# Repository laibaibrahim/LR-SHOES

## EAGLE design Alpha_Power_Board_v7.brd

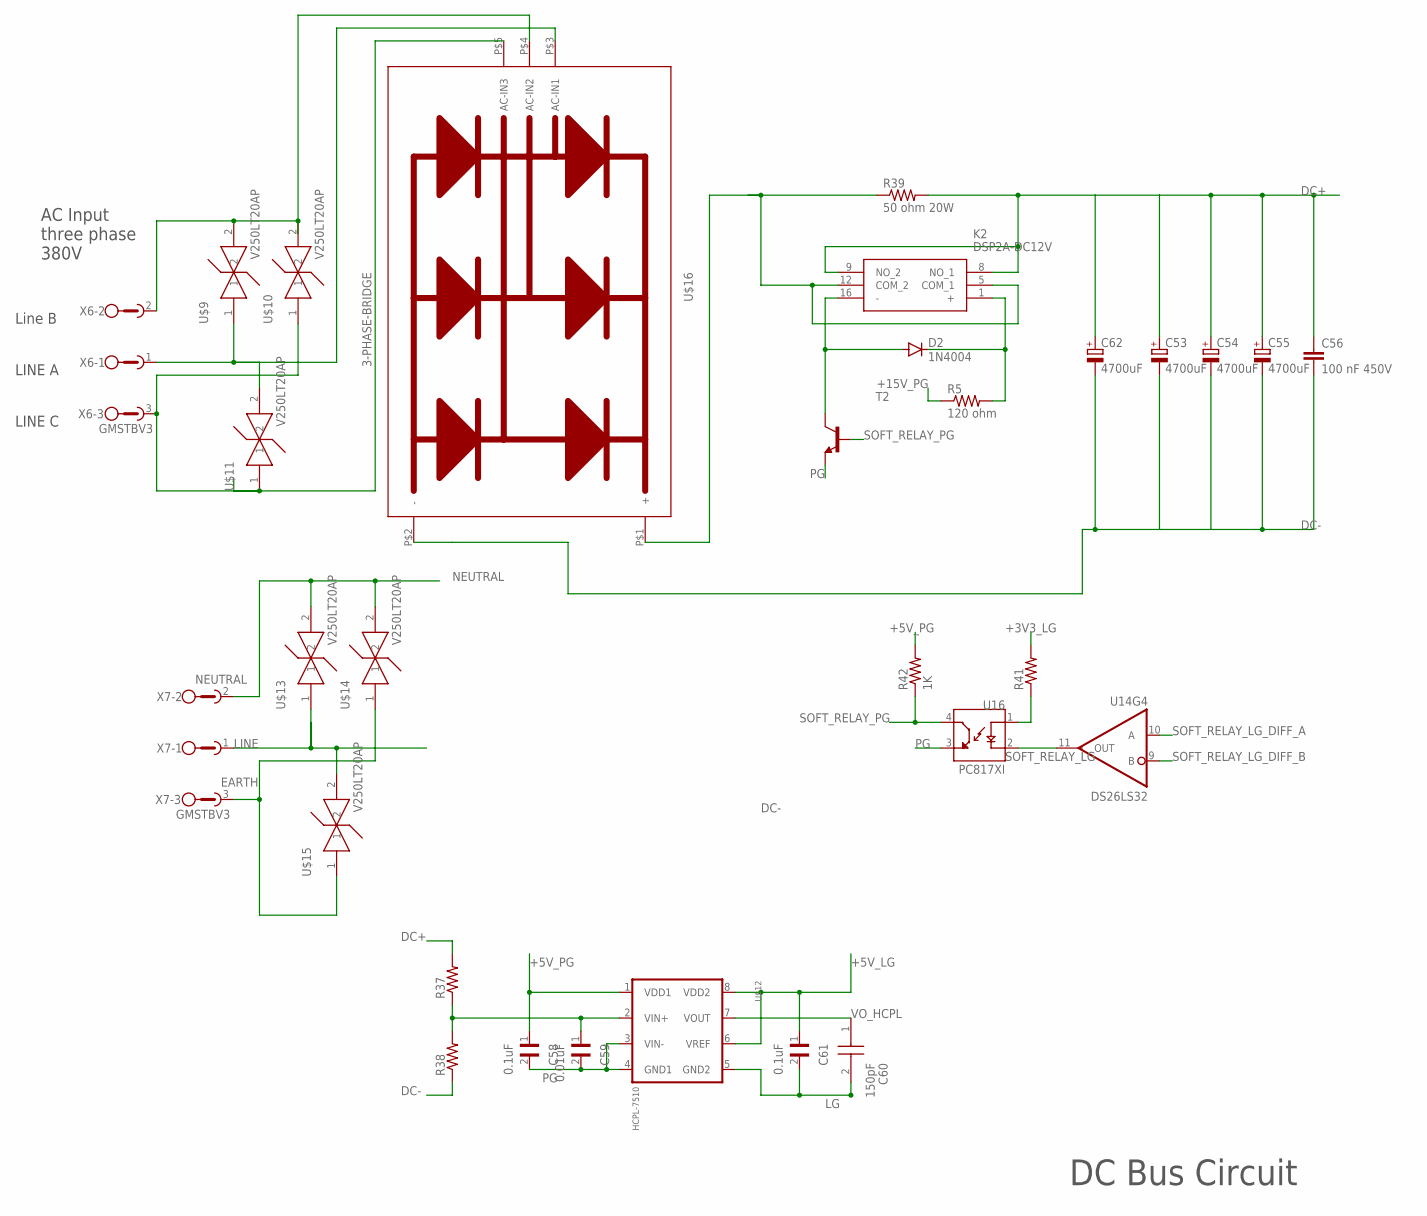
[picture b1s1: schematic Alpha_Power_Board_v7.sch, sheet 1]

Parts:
C53, C54, C55, C62: 4700uF; EB35D
C56: 100 nF 450V; C102-064X133
C58, C61: 0.1uF; CAPC3316X140N
C59: 0.01uF; CAPC3316X140N
C60: 150pF; CAP150PF
D2: 1N4004; DO41-10
K2: DSP2A-DC12V; DSP2ADC12V
R5: 120 ohm; 0207/15
R37, R38: R-US_0309/12; 0309/12
R39: 50 ohm 20W; B20J50RE
R41: R-US_R1206; R1206
R42: 1K; R1206
T2: MMBT2222ALT1-NPN-SOT23-BEC; SOT23-BEC
U14: DS26LS32; SOIC_16
U16: PC817XI; SOIC254P975X460-4N
U$9, U$10, U$11, U$13, U$14, U$15: V250LT20AP
U$12: HCPL-7510
U$16: 3-PHASE-BRIDGE
X6, X7: GMSTBV3

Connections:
+3V3_LG: R41.2; also elsewhere on the board
+5V_LG: C61.1, U$12.6 (VREF), U$12.8 (VDD2); also elsewhere on the board
+5V_PG: C58.1, R42.2, U$12.1 (VDD1); also elsewhere on the board
+15V_PG: R5.1; also elsewhere on the board
DC+: C53.+, C54.+, C55.+, C56.1, C62.+, K2.8 (NO_1), K2.9 (NO_2), R37.2, R39.2; also elsewhere on the board
DC-: C53.-, C54.-, C55.-, C56.2, C62.-, R38.1, U$16.P$2 (-); also elsewhere on the board
EARTH: U$14.1, U$15.1, X7.3
L1: U$9.1, U$11.2, U$16.P$3 (AC-IN1), X6.1
L2: U$9.2, U$10.2, U$16.P$4 (AC-IN2), X6.2
L3: U$10.1, U$11.1, U$16.P$5 (AC-IN3), X6.3
LG: C60.2, C61.2, U$12.5 (GND2); also elsewhere on the board
LINE: U$13.1, U$15.2, X7.1; also elsewhere on the board
unnamed: C59.1, R37.1, R38.2, U$12.2 (VIN+)
unnamed: D2.C, K2.1 (+), R5.2
unnamed: D2.A, K2.16 (-), T2.C
unnamed: R41.1, U16.1 (A)
unnamed: K2.5 (COM_1), K2.12 (COM_2), R39.1, U$16.P$1 (+)
NEUTRAL: U$13.2, U$14.2, X7.2; also elsewhere on the board
PG: C58.2, C59.2, T2.E, U16.3 (ET), U$12.3 (VIN-), U$12.4 (GND1); also elsewhere on the board
SOFT_RELAY_LG: U14.11 (OUT), U16.2 (C)
SOFT_RELAY_LG_DIFF_A: U14.10 (A); also elsewhere on the board
SOFT_RELAY_LG_DIFF_B: U14.9 (B); also elsewhere on the board
SOFT_RELAY_PG: R42.1, T2.B, U16.4 (CT)
VO_HCPL: C60.1, U$12.7 (VOUT); also elsewhere on the board

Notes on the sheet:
DC Bus Circuit
AC Input three phase 380V
Line B
LINE C
LINE A

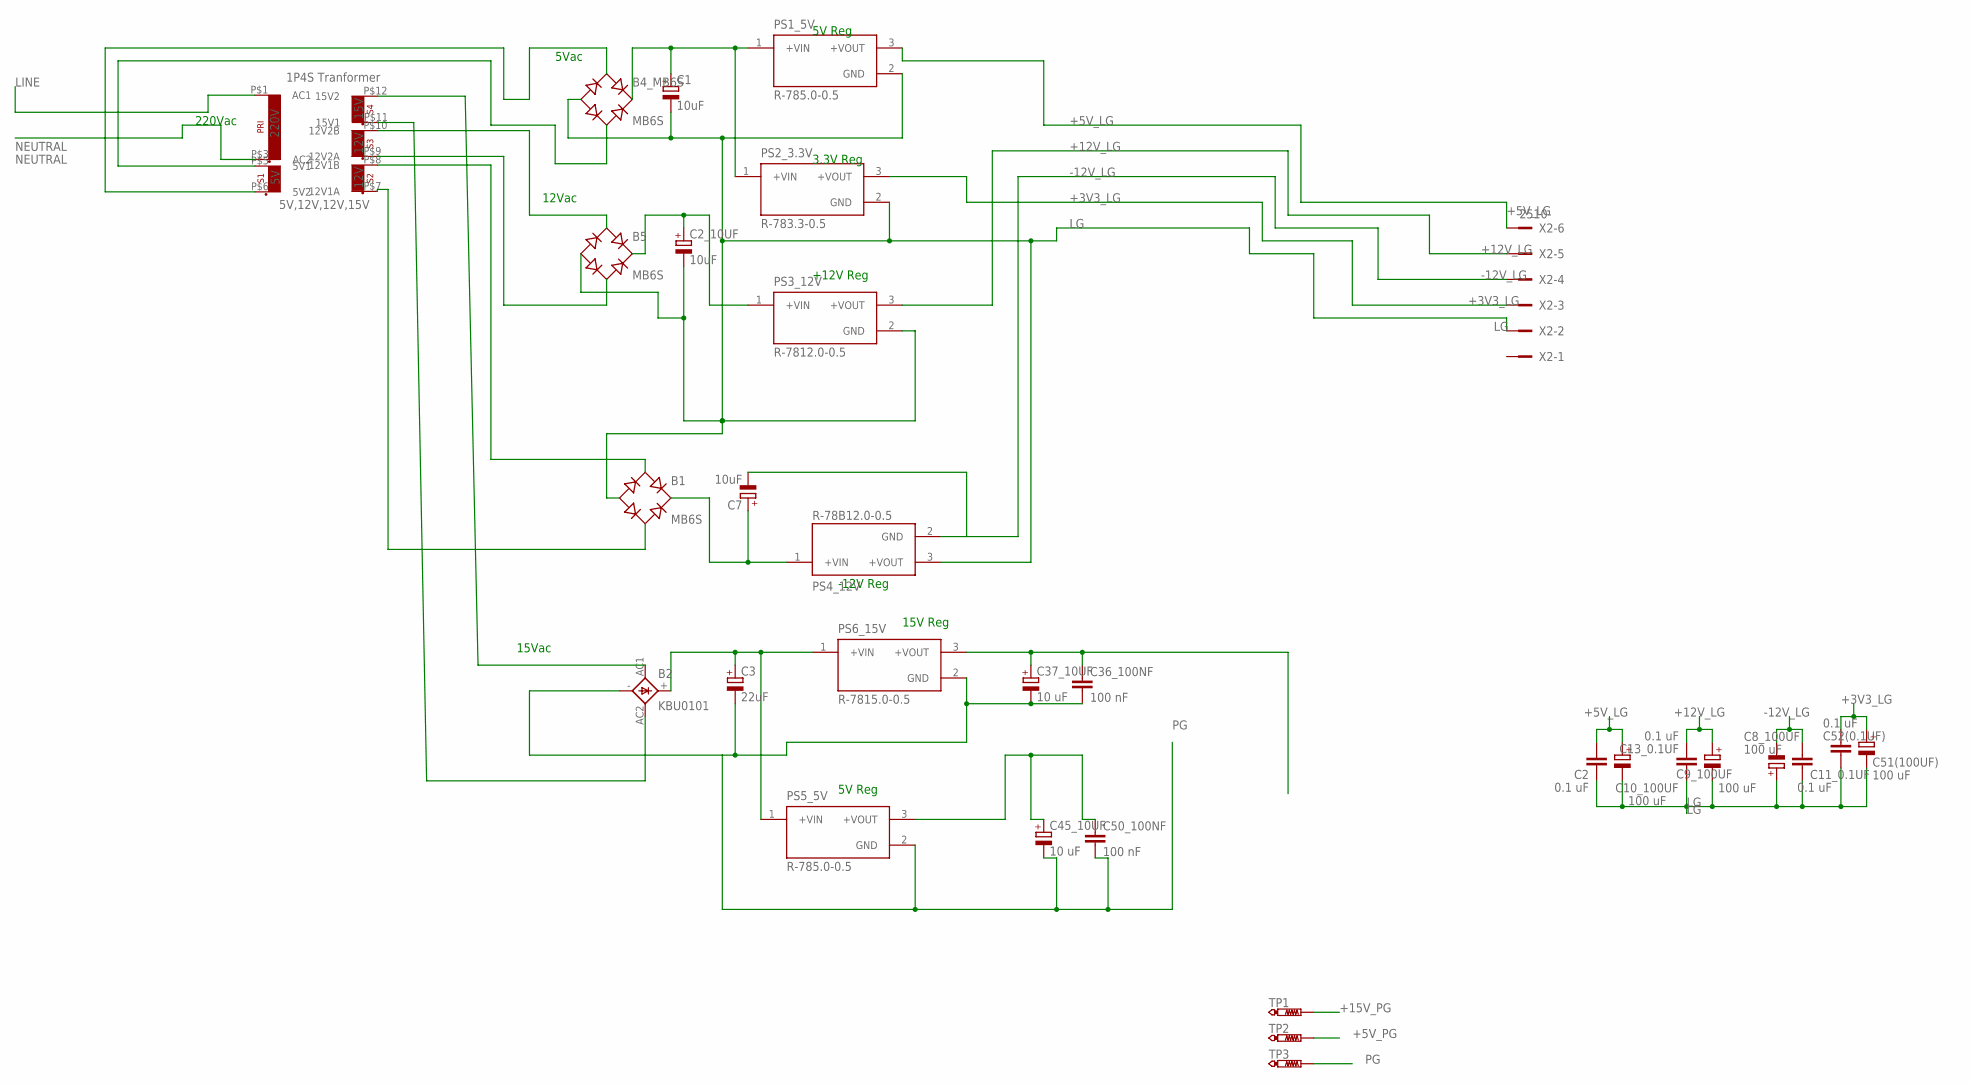
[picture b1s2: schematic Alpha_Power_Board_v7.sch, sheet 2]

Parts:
B1, B4_MB6S, B5: MB6S; SOIC-4
B2: KBU0101; KBU
C1, C2_10UF, C7: 10uF; E2,5-6E
C2, C11_0.1UF, C13_0.1UF, C52(0.1UF): 0.1 uF; C1206
C3: 22uF; E2,5-6E
C8_100UF, C9_100UF, C10_100UF, C51(100UF): 100 uF; 153CLV-0605
C36_100NF, C50_100NF: 100 nF; C025-025X050
C37_10UF, C45_10UF: 10 uF; TT2D5
PS1_5V, PS5_5V: R-785.0-0.5; CONV_R-78E5.0-0.5
PS2_3.3V: R-783.3-0.5; CONV_R-78E5.0-0.5
PS3_12V: R-7812.0-0.5; CONV_R-78E5.0-0.5
PS4_12V: R-78B12.0-0.5; CONV_R-78E5.0-0.5
PS6_15V: R-7815.0-0.5; CONV_R-78E5.0-0.5
TP1, TP2, TP3: PTR1PAD1-13; P1-13
U$1: TRANSFORMERTHROUGH-HOLE; T1P2S
X2: 2510-; PAK100/2500-10

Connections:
+3V3_LG: C51(100UF).+, C52(0.1UF).1, PS2_3.3V.3 (+VOUT), X2.3; also elsewhere on the board
+5V_LG: C2.1, C10_100UF.+, PS1_5V.3 (+VOUT), X2.6; also elsewhere on the board
+5V_PG: C45_10UF.+, C50_100NF.1, PS5_5V.3 (+VOUT), TP2.TP; also elsewhere on the board
+12V_LG: C9_100UF.+, C13_0.1UF.1, PS3_12V.3 (+VOUT), X2.5; also elsewhere on the board
+15V_PG: C36_100NF.1, C37_10UF.+, PS6_15V.3 (+VOUT), TP1.TP; also elsewhere on the board
-12V_LG: C7.-, C8_100UF.-, C11_0.1UF.1, PS4_12V.2 (GND), X2.4; also elsewhere on the board
LG: B1.-, B4_MB6S.-, B5.-, C1.-, C2.2, C2_10UF.-, C8_100UF.+, C9_100UF.-, C10_100UF.-, C11_0.1UF.2, C13_0.1UF.2, C51(100UF).-, C52(0.1UF).2, PS1_5V.2 (GND), PS2_3.3V.2 (GND), PS3_12V.2 (GND), PS4_12V.3 (+VOUT), X2.2; also elsewhere on the board
LINE: U$1.P$1 (AC1); also elsewhere on the board
unnamed: B4_MB6S.~2 (AC2), U$1.P$5 (5V1)
unnamed: B5.~1 (AC1), U$1.P$10 (12V2B)
unnamed: B5.~2 (AC2), U$1.P$9 (12V2A)
unnamed: B5.+, C2_10UF.+, PS3_12V.1 (+VIN)
unnamed: B2.AC1, U$1.P$12 (15V2)
unnamed: B2.AC2, U$1.P$11 (15V1)
unnamed: B4_MB6S.~1 (AC1), U$1.P$6 (5V2)
unnamed: B1.~1 (AC1), U$1.P$8 (12V1B)
unnamed: B1.~2 (AC2), U$1.P$7 (12V1A)
unnamed: B1.+, C7.+, PS4_12V.1 (+VIN)
unnamed: B2.+, C3.+, PS5_5V.1 (+VIN), PS6_15V.1 (+VIN)
unnamed: B4_MB6S.+, C1.+, PS1_5V.1 (+VIN), PS2_3.3V.1 (+VIN)
NEUTRAL: U$1.P$3 (AC2); also elsewhere on the board
PG: B2.-, C3.-, C36_100NF.2, C37_10UF.-, C45_10UF.-, C50_100NF.2, PS5_5V.2 (GND), PS6_15V.2 (GND), TP3.TP; also elsewhere on the board

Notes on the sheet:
5Vac
5V Reg
3.3V Reg
12Vac
+12V Reg
15Vac
220Vac
15V Reg
-12V Reg

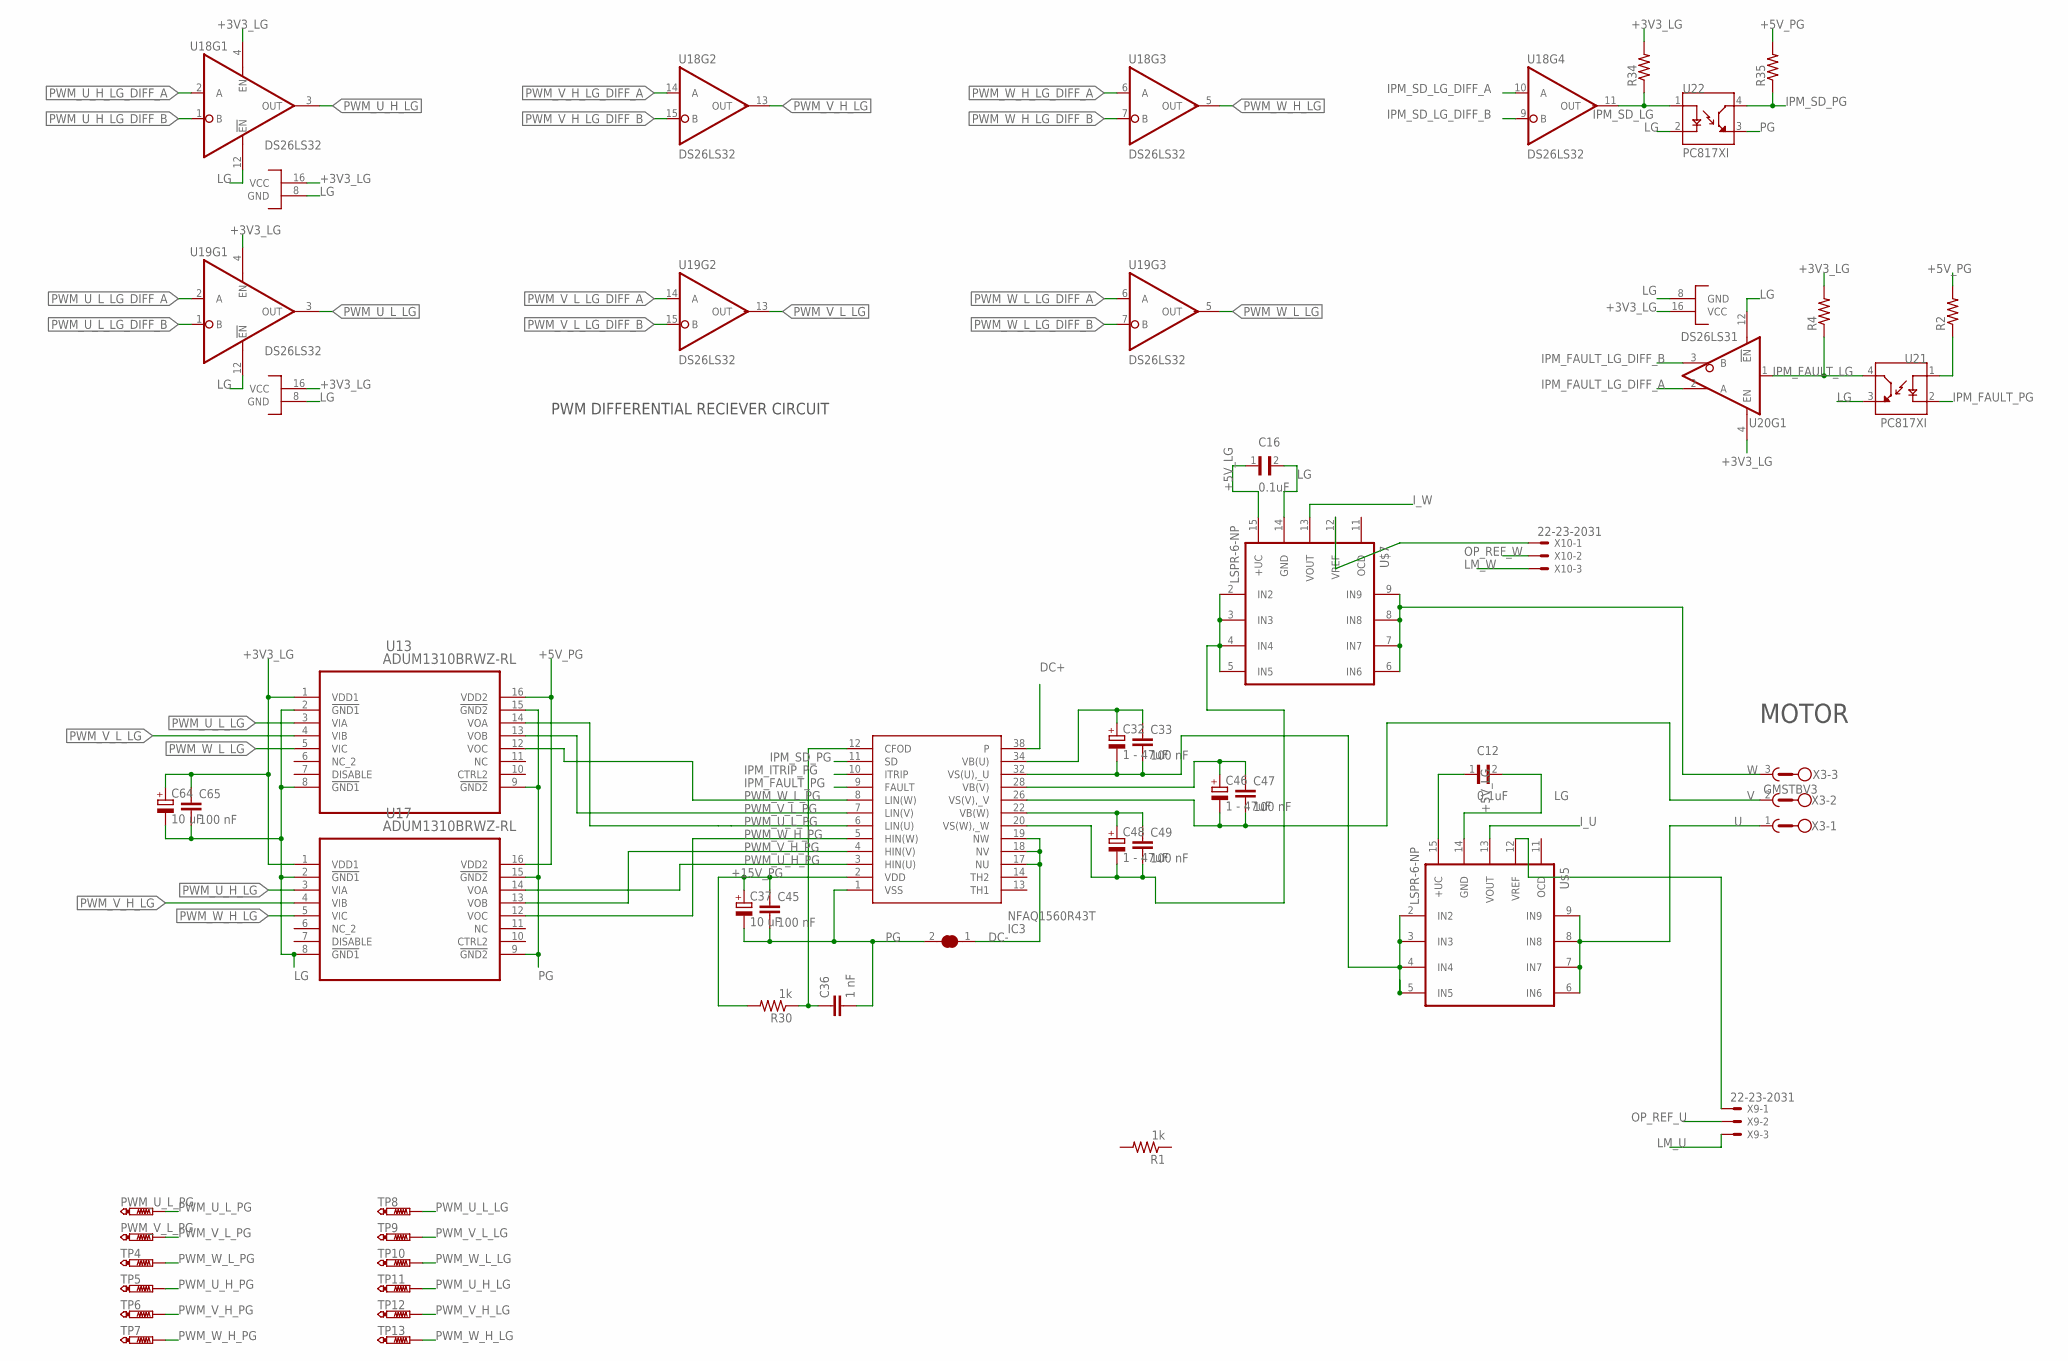
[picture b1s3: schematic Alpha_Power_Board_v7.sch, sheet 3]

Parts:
C12, C16: 0.1uF; CAPC3316X140N
C32, C46, C48: 1 - 47uF; E3,5-8
C33, C47, C49: 100 nF; C025-030X050
C36: 1 nF; C025-025X050
C37: 10 uF; TT2D5
C45: 100 nF; C025-025X050
C64: 10 uF; SMC_P
C65: 100 nF; C1206
IC3: NFAQ1560R43T
PWM_U_L_PG: PTR1PAD1-13; P1-13
PWM_V_L_PG: PTR1PAD1-13; P1-13
R1, R30: 1k; 0204V
R2, R4: R-US_R1206; R1206
R34: R-US_R0805W; R0805W
R35: R-US_R0805; R0805
TP4, TP5, TP6, TP7, TP8, TP9, TP10, TP11, TP12, TP13: PTR1PAD1-13; P1-13
U13, U17: ADUM1310BRWZ-RL; RW_16_ADI
U18, U19: DS26LS32; SOIC_16
U20: DS26LS31; SOIC_16
U21, U22: PC817XI; SOIC254P975X460-4N
U$2: GND_CONNECT
U$5, U$7: LSPR-6-NP; LPSR-15-NP
X3: GMSTBV3
X9, X10: 22-23-2031

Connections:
+3V3_LG: C64.+, C65.1, R4.2, R34.2, U13.1 (VDD1), U17.1 (VDD1), U18.4 (EN), U18.16 (VCC), U19.4 (EN), U19.16 (VCC), U20.4 (EN), U20.16 (VCC); also elsewhere on the board
+5V_LG: C12.1, C16.1, U$5.15 (+UC), U$7.15 (+UC); also elsewhere on the board
+5V_PG: R2.2, R35.2, U13.16 (VDD2), U17.16 (VDD2); also elsewhere on the board
+15V_PG: C37.+, C45.1, IC3.2 (VDD), R30.2; also elsewhere on the board
DC+: IC3.38; also elsewhere on the board
DC-: IC3.17 (NU), IC3.18 (NV), IC3.19 (NW), U$2.1; also elsewhere on the board
IPM_FAULT_LG: R4.1, U20.1 (IN), U21.4 (CT)
IPM_FAULT_LG_DIFF_A: U20.2 (A); also elsewhere on the board
IPM_FAULT_LG_DIFF_B: U20.3 (B); also elsewhere on the board
IPM_FAULT_PG: IC3.9 (FAULT), U21.2 (C)
IPM_ITRIP_PG: IC3.10 (ITRIP)
IPM_SD_LG: R34.1, U18.11 (OUT), U22.1 (A)
IPM_SD_LG_DIFF_A: U18.10 (A); also elsewhere on the board
IPM_SD_LG_DIFF_B: U18.9 (B); also elsewhere on the board
IPM_SD_PG: IC3.11 (SD), R35.1, U22.4 (CT)
I_U: U$5.13 (VOUT); also elsewhere on the board
I_W: U$7.13 (VOUT); also elsewhere on the board
LG: C12.2, C16.2, C64.-, C65.2, U13.2 (!GND1), U13.8 (!GND1), U17.2 (!GND1), U17.8 (!GND1), U18.8 (GND), U18.12 (!EN), U19.8 (GND), U19.12 (!EN), U20.8 (GND), U20.12 (!EN), U21.3 (ET), U22.2 (C), U$5.14 (GND), U$7.14 (GND); also elsewhere on the board
LM_U: X9.3; also elsewhere on the board
LM_W: X10.3; also elsewhere on the board
unnamed: R2.1, U21.1 (A)
unnamed: U$5.12 (VREF), X9.1
unnamed: C32.-, C33.2, IC3.32 (VS(U),_U), U$5.2 (IN2), U$5.3 (IN3), U$5.4 (IN4), U$5.5 (IN5)
unnamed: U$7.12 (VREF), X10.1
unnamed: C32.+, C33.1, IC3.34 (VB(U))
unnamed: C48.+, C49.1, IC3.22 (VB(W))
unnamed: C48.-, C49.2, IC3.20 (VS(W),_W), U$7.2 (IN2), U$7.3 (IN3), U$7.4 (IN4), U$7.5 (IN5)
unnamed: C46.+, C47.1, IC3.28 (VB(V))
unnamed: C36.1, IC3.12 (CFOD), R30.1
OP_REF_U: X9.2; also elsewhere on the board
OP_REF_W: X10.2; also elsewhere on the board
PG: C36.2, C37.-, C45.2, IC3.1 (VSS), U13.9 (!GND2), U13.15 (!GND2), U17.9 (!GND2), U17.15 (!GND2), U22.3 (ET), U$2.2; also elsewhere on the board
PWM_U_H_LG: TP11.TP, U17.3 (VIA), U18.3 (OUT)
PWM_U_H_LG_DIFF_A: U18.2 (A); also elsewhere on the board
PWM_U_H_LG_DIFF_B: U18.1 (B); also elsewhere on the board
PWM_U_H_PG: IC3.3 (HIN(U)), TP5.TP, U17.14 (VOA)
PWM_U_L_LG: TP8.TP, U13.3 (VIA), U19.3 (OUT)
PWM_U_L_LG_DIFF_A: U19.2 (A); also elsewhere on the board
PWM_U_L_LG_DIFF_B: U19.1 (B); also elsewhere on the board
PWM_U_L_PG: IC3.6 (LIN(U)), PWM_U_L_PG.TP, U13.14 (VOA)
PWM_V_H_LG: TP12.TP, U17.4 (VIB), U18.13 (OUT)
PWM_V_H_LG_DIFF_A: U18.14 (A); also elsewhere on the board
PWM_V_H_LG_DIFF_B: U18.15 (B); also elsewhere on the board
PWM_V_H_PG: IC3.4 (HIN(V)), TP6.TP, U17.13 (VOB)
PWM_V_L_LG: TP9.TP, U13.4 (VIB), U19.13 (OUT)
PWM_V_L_LG_DIFF_A: U19.14 (A); also elsewhere on the board
PWM_V_L_LG_DIFF_B: U19.15 (B); also elsewhere on the board
PWM_V_L_PG: IC3.7 (LIN(V)), PWM_V_L_PG.TP, U13.13 (VOB)
PWM_W_H_LG: TP13.TP, U17.5 (VIC), U18.5 (OUT)
PWM_W_H_LG_DIFF_A: U18.6 (A); also elsewhere on the board
PWM_W_H_LG_DIFF_B: U18.7 (B); also elsewhere on the board
PWM_W_H_PG: IC3.5 (HIN(W)), TP7.TP, U17.12 (VOC)
PWM_W_L_LG: TP10.TP, U13.5 (VIC), U19.5 (OUT)
PWM_W_L_LG_DIFF_A: U19.6 (A); also elsewhere on the board
PWM_W_L_LG_DIFF_B: U19.7 (B); also elsewhere on the board
PWM_W_L_PG: IC3.8 (LIN(W)), TP4.TP, U13.12 (VOC)
U: U$5.6 (IN6), U$5.7 (IN7), U$5.8 (IN8), U$5.9 (IN9), X3.1
V: C46.-, C47.2, IC3.26 (VS(V),_V), X3.2
W: U$7.6 (IN6), U$7.7 (IN7), U$7.8 (IN8), U$7.9 (IN9), X3.3

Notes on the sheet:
MOTOR
PWM DIFFERENTIAL RECIEVER CIRCUIT

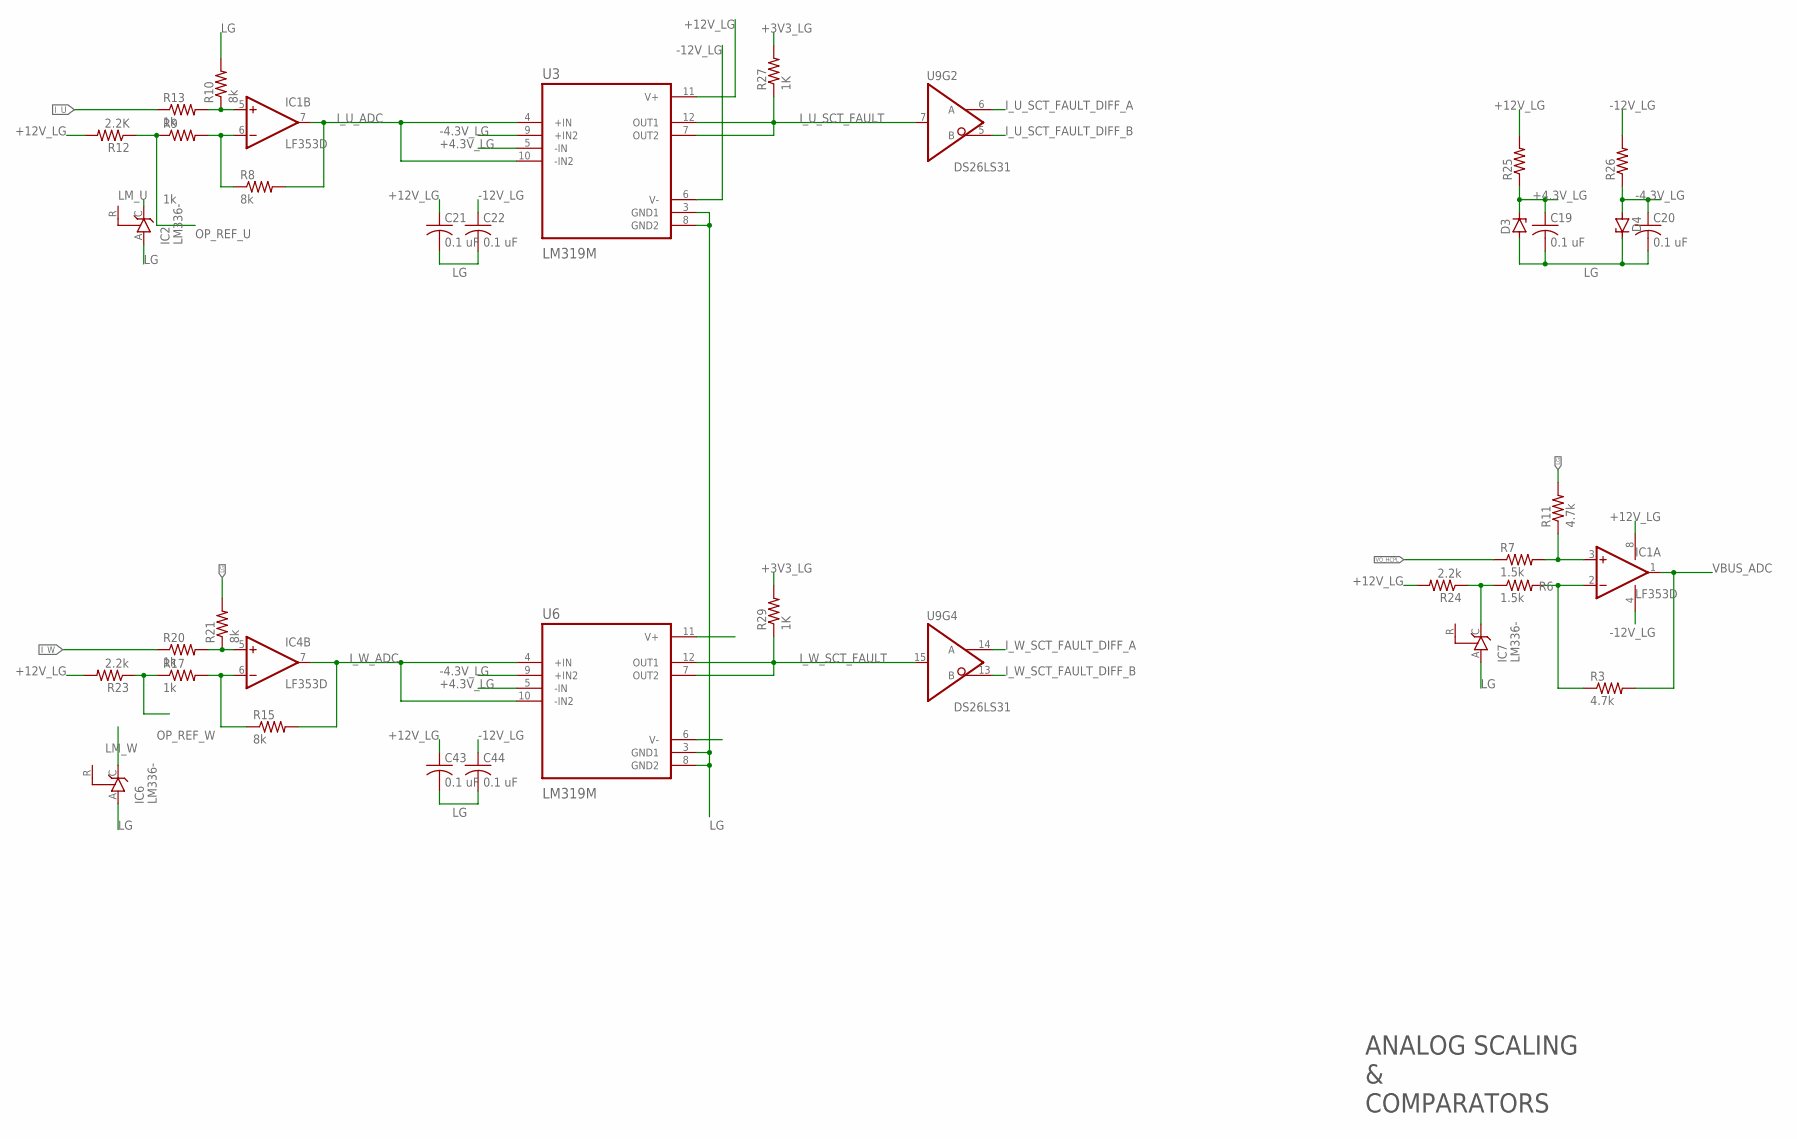
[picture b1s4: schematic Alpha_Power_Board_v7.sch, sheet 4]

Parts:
C19, C20, C21, C22, C43, C44: 0.1 uF; C1206
D3, D4: ZENER-DIODETO236; TO236
IC1, IC4: LF353D; SO08
IC2, IC6, IC7: LM336-; TO92A_VREF
R3, R11: 4.7k; M1206
R6: 1.5k; M1206
R7: 1.5k; R1206
R8, R10, R15, R21: 8k; M1206
R9, R13, R17, R20: 1k; M1206
R12: 2.2K; M1206
R23, R24: 2.2k; M1206
R25, R26: R-US_M1206; M1206
R27, R29: 1K; R1206
U3, U6: LM319M; SOIC127P600X175-14N
U9: DS26LS31; SOIC_16

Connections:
+3V3_LG: R27.2, R29.2; also elsewhere on the board
+4.3V_LG: C19.1, D3.C, R25.1, U3.5 (-IN), U6.5 (-IN)
+12V_LG: C21.1, C43.1, IC1.8 (V+), R12.2, R23.2, R24.2, R25.2, U3.11 (V+); also elsewhere on the board
-4.3V_LG: C20.1, D4.A, R26.1, U3.9 (+IN2), U6.9 (+IN2)
-12V_LG: C22.1, C44.1, IC1.4 (V-), R26.2, U3.6 (V-); also elsewhere on the board
I_U: R13.1; also elsewhere on the board
I_U_ADC: IC1.7 (OUT), R8.2, U3.4 (+IN), U3.10 (-IN2); also elsewhere on the board
I_U_SCT_FAULT: R27.1, U3.7 (OUT2), U3.12 (OUT1), U9.7 (IN)
I_U_SCT_FAULT_DIFF_A: U9.6 (A); also elsewhere on the board
I_U_SCT_FAULT_DIFF_B: U9.5 (B); also elsewhere on the board
I_W: R20.1; also elsewhere on the board
I_W_ADC: IC4.7 (OUT), R15.2, U6.4 (+IN), U6.10 (-IN2); also elsewhere on the board
I_W_SCT_FAULT: R29.1, U6.7 (OUT2), U6.12 (OUT1), U9.15 (IN)
I_W_SCT_FAULT_DIFF_A: U9.14 (A); also elsewhere on the board
I_W_SCT_FAULT_DIFF_B: U9.13 (B); also elsewhere on the board
LG: C19.2, C20.2, C21.2, C22.2, C43.2, C44.2, D3.A, D4.C, IC2.A, IC6.A, IC7.A, R10.2, R11.2, R21.2, U3.3 (GND1), U3.8 (GND2), U6.3 (GND1), U6.8 (GND2); also elsewhere on the board
LM_U: IC2.C; also elsewhere on the board
LM_W: IC6.C; also elsewhere on the board
unnamed: IC1.6 (-IN), R8.1, R9.2
unnamed: IC1.3 (+IN), R7.2, R11.1
unnamed: IC4.6 (-IN), R15.1, R17.2
unnamed: IC1.2 (-IN), R3.1, R6.2
unnamed: IC1.5 (+IN), R10.1, R13.2
unnamed: IC4.5 (+IN), R20.2, R21.1
unnamed: IC7.C, R6.1, R24.1
OP_REF_U: R9.1, R12.1; also elsewhere on the board
OP_REF_W: R17.1, R23.1; also elsewhere on the board
V+: IC4.8 (V+)
V-: IC4.4 (V-)
VBUS_ADC: IC1.1 (OUT), R3.2; also elsewhere on the board
VO_HCPL: R7.1; also elsewhere on the board

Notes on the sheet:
ANALOG SCALING & COMPARATORS

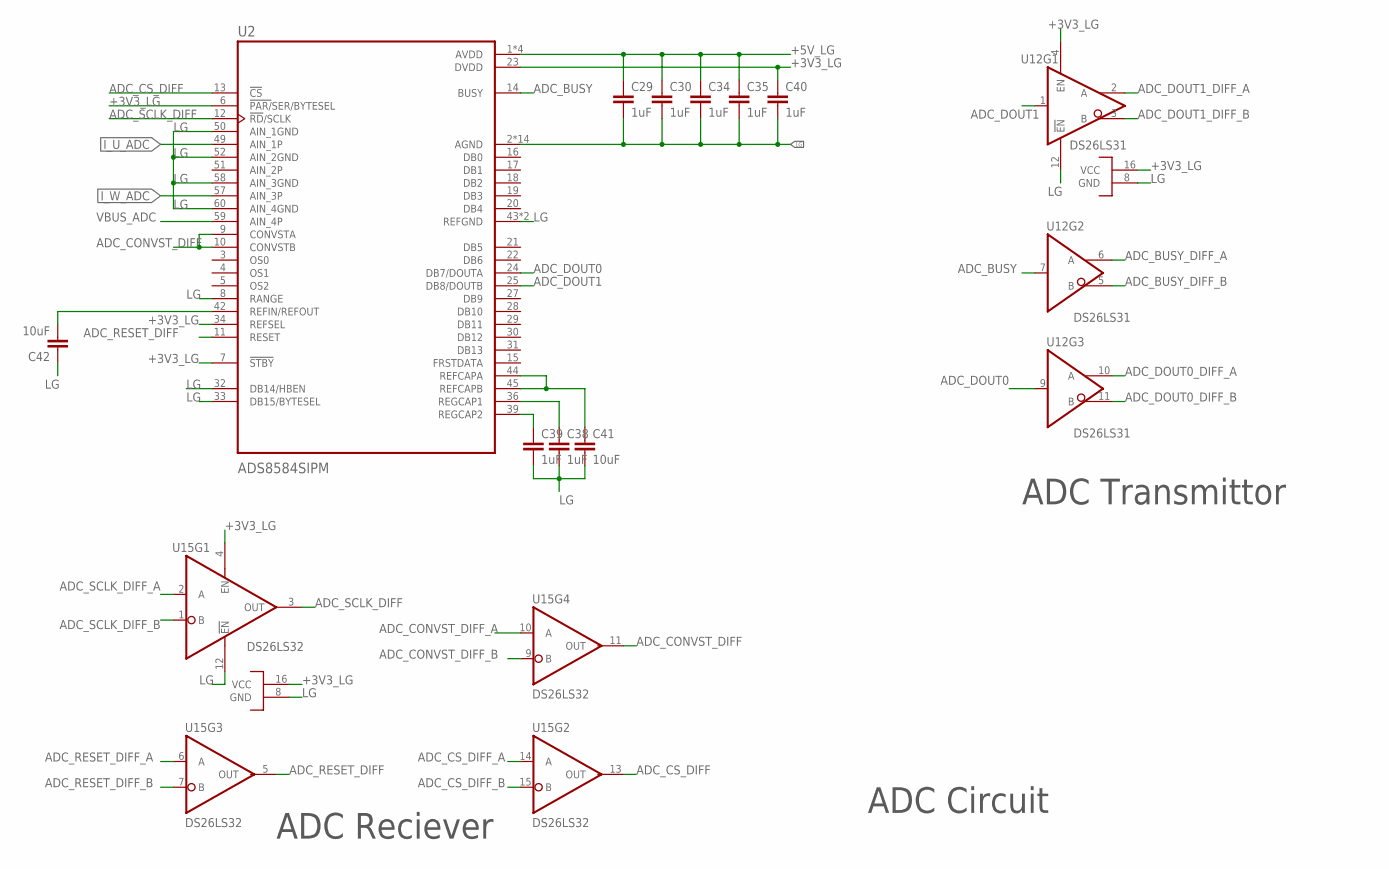
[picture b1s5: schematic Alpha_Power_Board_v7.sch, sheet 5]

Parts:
C29, C30, C34, C35, C38, C39, C40: 1uF; C0603
C41, C42: 10uF; C0603
U2: ADS8584SIPM; QFP50P1200X1200X160-64N
U12: DS26LS31; SOIC_16
U15: DS26LS32; SOIC_16

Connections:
+3V3_LG: C40.1, U2.6 (!PAR/!SER/BYTESEL), U2.7 (!STBY), U2.23 (DVDD), U2.34 (REFSEL), U12.4 (EN), U12.16 (VCC), U15.4 (EN), U15.16 (VCC); also elsewhere on the board
+5V_LG: C29.1, C30.1, C34.1, C35.1, U2.1 (AVDD), U2.37 (AVDD), U2.38 (AVDD), U2.48 (AVDD); also elsewhere on the board
ADC_BUSY: U2.14 (BUSY), U12.7 (IN)
ADC_BUSY_DIFF_A: U12.6 (A); also elsewhere on the board
ADC_BUSY_DIFF_B: U12.5 (B); also elsewhere on the board
ADC_CONVST_DIFF: U2.9 (CONVSTA), U2.10 (CONVSTB), U15.11 (OUT)
ADC_CONVST_DIFF_A: U15.10 (A); also elsewhere on the board
ADC_CONVST_DIFF_B: U15.9 (B); also elsewhere on the board
ADC_CS_DIFF: U2.13 (!CS), U15.13 (OUT)
ADC_CS_DIFF_A: U15.14 (A); also elsewhere on the board
ADC_CS_DIFF_B: U15.15 (B); also elsewhere on the board
ADC_DOUT0: U2.24 (DB7/DOUTA), U12.9 (IN)
ADC_DOUT0_DIFF_A: U12.10 (A); also elsewhere on the board
ADC_DOUT0_DIFF_B: U12.11 (B); also elsewhere on the board
ADC_DOUT1: U2.25 (DB8/DOUTB), U12.1 (IN)
ADC_DOUT1_DIFF_A: U12.2 (A); also elsewhere on the board
ADC_DOUT1_DIFF_B: U12.3 (B); also elsewhere on the board
ADC_RESET_DIFF: U2.11 (RESET), U15.5 (OUT)
ADC_RESET_DIFF_A: U15.6 (A); also elsewhere on the board
ADC_RESET_DIFF_B: U15.7 (B); also elsewhere on the board
ADC_SCLK_DIFF: U2.12 (!RD!/SCLK), U15.3 (OUT)
ADC_SCLK_DIFF_A: U15.2 (A); also elsewhere on the board
ADC_SCLK_DIFF_B: U15.1 (B); also elsewhere on the board
I_U_ADC: U2.49 (AIN_1P); also elsewhere on the board
I_W_ADC: U2.57 (AIN_3P); also elsewhere on the board
LG: C29.2, C30.2, C34.2, C35.2, C38.2, C39.2, C40.2, C41.2, C42.1, U2.2 (AGND), U2.8 (RANGE), U2.26 (AGND), U2.32 (DB14/HBEN), U2.33 (DB15/BYTESEL), U2.35 (AGND), U2.40 (AGND), U2.41 (AGND), U2.43 (REFGND), U2.46 (REFGND), U2.47 (AGND), U2.50 (AIN_1GND), U2.52 (AIN_2GND), U2.53 (AGND), U2.54 (AGND), U2.55 (AGND), U2.56 (AGND), U2.58 (AIN_3GND), U2.60 (AIN_4GND), U2.61 (AGND), U2.62 (AGND), U2.63 (AGND), U2.64 (AGND), U12.8 (GND), U12.12 (!EN), U15.8 (GND), U15.12 (!EN); also elsewhere on the board
unnamed: C39.1, U2.39 (REGCAP2)
unnamed: C42.2, U2.42 (REFIN/REFOUT)
unnamed: C38.1, U2.36 (REGCAP1)
unnamed: C41.1, U2.44 (REFCAPA), U2.45 (REFCAPB)
VBUS_ADC: U2.59 (AIN_4P); also elsewhere on the board

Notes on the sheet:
ADC Circuit
ADC Reciever
ADC Transmittor

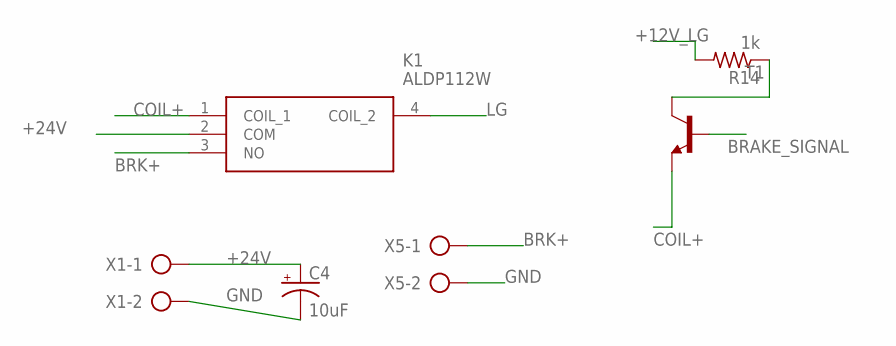
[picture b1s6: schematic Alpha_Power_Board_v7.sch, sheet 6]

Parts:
C4: 10uF; E2,5-6E
K1: ALDP112W
R14: 1k; 0204V
T1: MMBT2222ALT1-NPN-SOT23-BEC; SOT23-BEC
X1, X5: AK500/2-H

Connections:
+12V_LG: R14.2; also elsewhere on the board
+24V: C4.+, K1.2 (COM), X1.1
BRAKE_SIGNAL: T1.B
BRK+: K1.3 (NO), X5.1
COIL+: K1.1 (COIL_1), T1.E
GND: C4.-, X1.2, X5.2
LG: K1.4 (COIL_2); also elsewhere on the board
unnamed: R14.1, T1.C

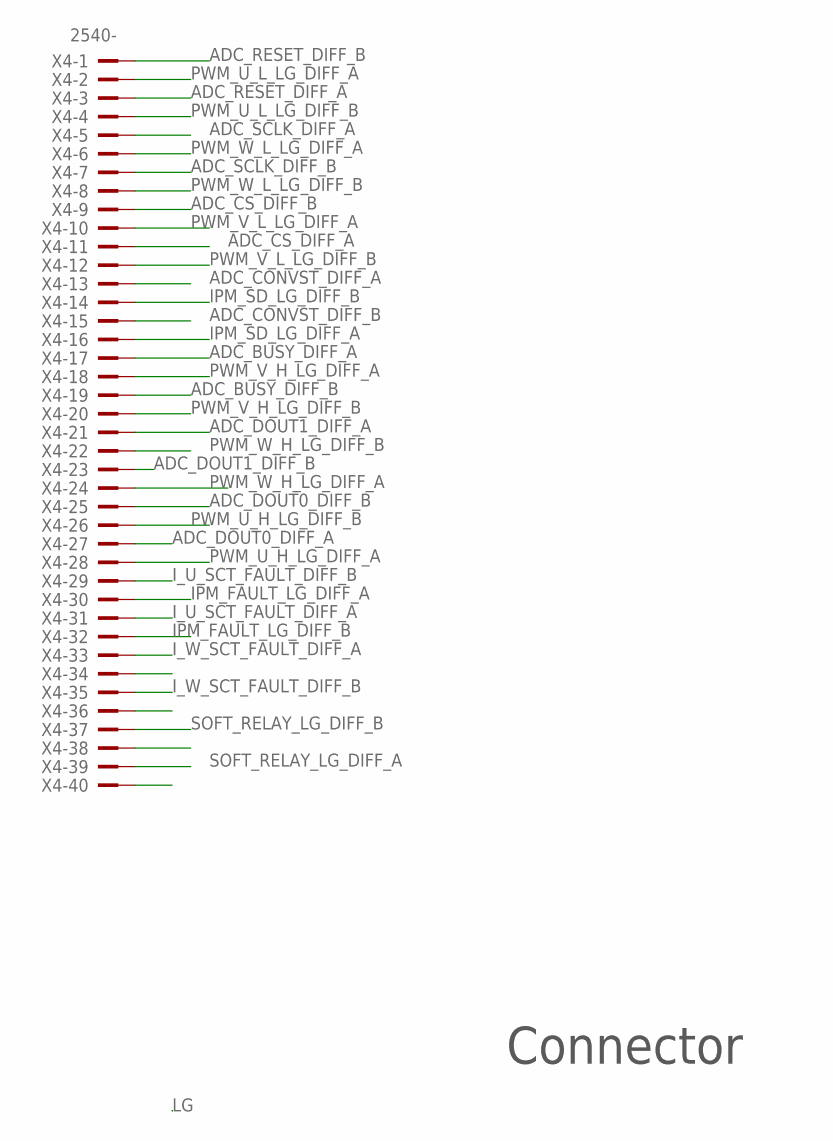
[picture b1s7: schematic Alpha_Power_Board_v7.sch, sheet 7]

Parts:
X4: 2540-; PAK100/2500-40

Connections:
ADC_BUSY_DIFF_A: X4.17; also elsewhere on the board
ADC_BUSY_DIFF_B: X4.19; also elsewhere on the board
ADC_CONVST_DIFF_A: X4.13; also elsewhere on the board
ADC_CONVST_DIFF_B: X4.15; also elsewhere on the board
ADC_CS_DIFF_A: X4.11; also elsewhere on the board
ADC_CS_DIFF_B: X4.9; also elsewhere on the board
ADC_DOUT0_DIFF_A: X4.27; also elsewhere on the board
ADC_DOUT0_DIFF_B: X4.25; also elsewhere on the board
ADC_DOUT1_DIFF_A: X4.21; also elsewhere on the board
ADC_DOUT1_DIFF_B: X4.23; also elsewhere on the board
ADC_RESET_DIFF_A: X4.3; also elsewhere on the board
ADC_RESET_DIFF_B: X4.1; also elsewhere on the board
ADC_SCLK_DIFF_A: X4.5; also elsewhere on the board
ADC_SCLK_DIFF_B: X4.7; also elsewhere on the board
IPM_FAULT_LG_DIFF_A: X4.30; also elsewhere on the board
IPM_FAULT_LG_DIFF_B: X4.32; also elsewhere on the board
IPM_SD_LG_DIFF_A: X4.16; also elsewhere on the board
IPM_SD_LG_DIFF_B: X4.14; also elsewhere on the board
I_U_SCT_FAULT_DIFF_A: X4.31; also elsewhere on the board
I_U_SCT_FAULT_DIFF_B: X4.29; also elsewhere on the board
I_W_SCT_FAULT_DIFF_A: X4.33; also elsewhere on the board
I_W_SCT_FAULT_DIFF_B: X4.34, X4.35; also elsewhere on the board
PWM_U_H_LG_DIFF_A: X4.28; also elsewhere on the board
PWM_U_H_LG_DIFF_B: X4.26; also elsewhere on the board
PWM_U_L_LG_DIFF_A: X4.2; also elsewhere on the board
PWM_U_L_LG_DIFF_B: X4.4; also elsewhere on the board
PWM_V_H_LG_DIFF_A: X4.18; also elsewhere on the board
PWM_V_H_LG_DIFF_B: X4.20; also elsewhere on the board
PWM_V_L_LG_DIFF_A: X4.10; also elsewhere on the board
PWM_V_L_LG_DIFF_B: X4.12; also elsewhere on the board
PWM_W_H_LG_DIFF_A: X4.24; also elsewhere on the board
PWM_W_H_LG_DIFF_B: X4.22; also elsewhere on the board
PWM_W_L_LG_DIFF_A: X4.6; also elsewhere on the board
PWM_W_L_LG_DIFF_B: X4.8; also elsewhere on the board
SOFT_RELAY_LG_DIFF_A: X4.39; also elsewhere on the board
SOFT_RELAY_LG_DIFF_B: X4.37; also elsewhere on the board

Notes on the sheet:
Connector

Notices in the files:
parts and their libraries:
COPYRIGHT: Copyright (C) 2018 Accelerated Designs. All rights reserved
